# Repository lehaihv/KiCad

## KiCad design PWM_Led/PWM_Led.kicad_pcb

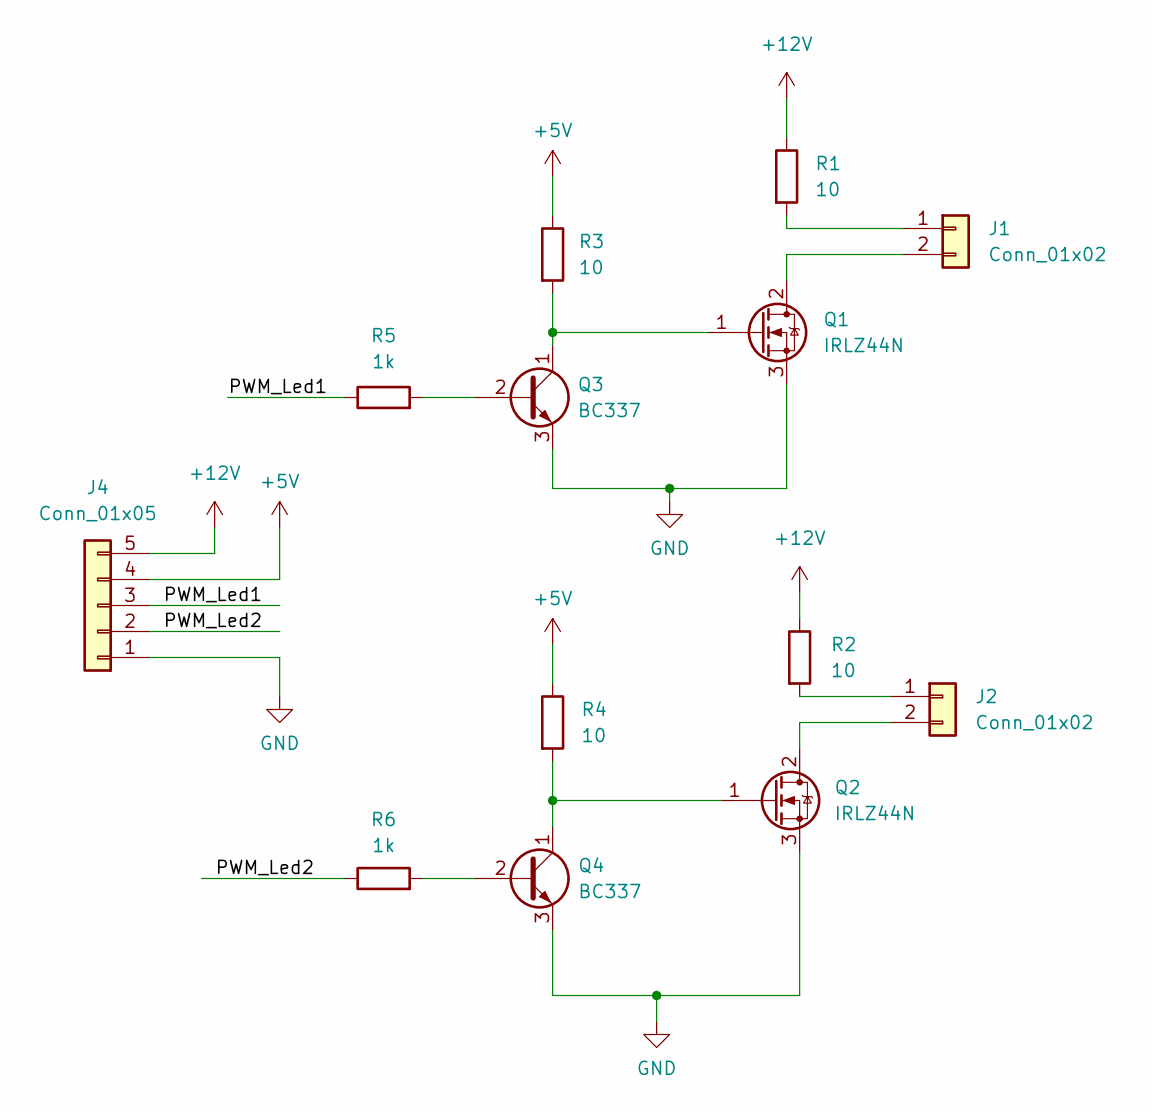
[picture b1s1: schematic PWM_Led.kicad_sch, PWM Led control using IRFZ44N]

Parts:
J1, J2: Conn_01x02
J4: Conn_01x05
Q1, Q2: IRLZ44N; TO-220-3_Vertical
Q3, Q4: BC337; TO-92_Inline
R1, R2, R3, R4: 10
R5, R6: 1k

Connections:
+5V: J4.4, R3.1, R4.1
+12V: J4.5, R1.1, R2.1
/PWM_Led1: J4.3, R5.1
/PWM_Led2: J4.2, R6.1
GND: J4.1, Q1.3 (S), Q2.3 (S), Q3.3 (E), Q4.3 (E)
unnamed: J1.1, R1.2
unnamed: J1.2, Q1.2 (D)
unnamed: J2.1, R2.2
unnamed: J2.2, Q2.2 (D)
unnamed: Q1.1 (G), Q3.1 (C), R3.2
unnamed: Q2.1 (G), Q4.1 (C), R4.2
unnamed: Q3.2 (B), R5.2
unnamed: Q4.2 (B), R6.2

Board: 2 copper layers, 13 parts (0 on the bottom side), 13 nets, no tracks yet.

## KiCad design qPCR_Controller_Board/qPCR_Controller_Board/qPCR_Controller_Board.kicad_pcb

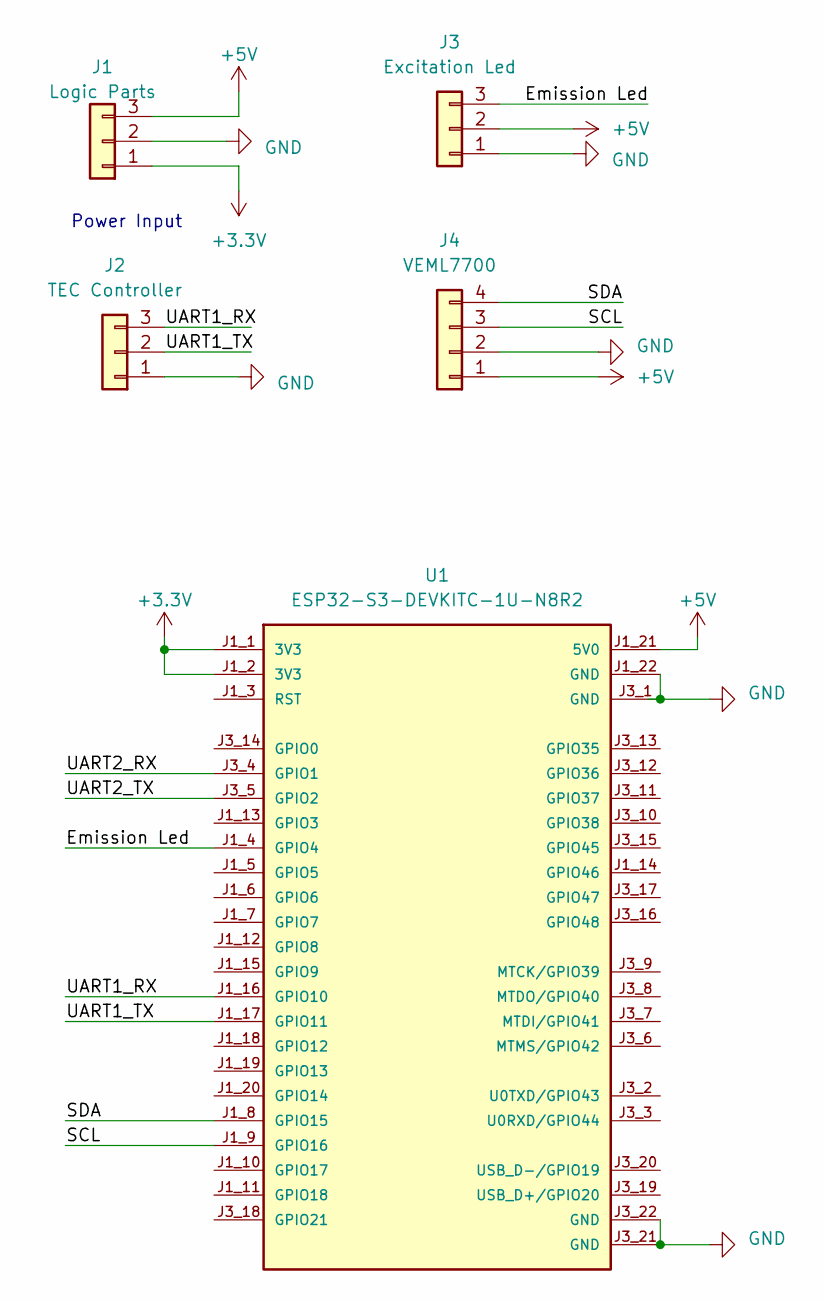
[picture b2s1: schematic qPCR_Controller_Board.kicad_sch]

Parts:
J1: Logic Parts; Molex_KK-254_AE-6410-03A_1x03_P2.54mm_Vertical
J2: TEC Controller; Molex_KK-254_AE-6410-03A_1x03_P2.54mm_Vertical
J3: Excitation Led; Molex_KK-254_AE-6410-03A_1x03_P2.54mm_Vertical
J4: VEML7700; Molex_KK-254_AE-6410-04A_1x04_P2.54mm_Vertical
U1: ESP32-S3-DEVKITC-1U-N8R2; XCVR_ESP32-S3-DEVKITC-1U-N8R2; PARTREV 5.3

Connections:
+3.3V: J1.1, U1.J1_1 (3V3), U1.J1_2 (3V3)
+5V: J1.3, J3.2, J4.1, U1.J1_21 (5V0)
/Emission Led: J3.3, U1.J1_4 (GPIO4)
/SCL: J4.3, U1.J1_9 (GPIO16)
/SDA: J4.4, U1.J1_8 (GPIO15)
/UART1_RX: J2.3, U1.J1_16 (GPIO10)
/UART1_TX: J2.2, U1.J1_17 (GPIO11)
/UART2_RX: U1.J3_4 (GPIO1)
/UART2_TX: U1.J3_5 (GPIO2)
GND: J1.2, J2.1, J3.1, J4.2, U1.J1_22 (GND), U1.J3_1 (GND), U1.J3_21 (GND), U1.J3_22 (GND)

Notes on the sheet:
Power Input

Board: 2 copper layers, 5 parts (0 on the bottom side), 8 nets, no tracks yet.

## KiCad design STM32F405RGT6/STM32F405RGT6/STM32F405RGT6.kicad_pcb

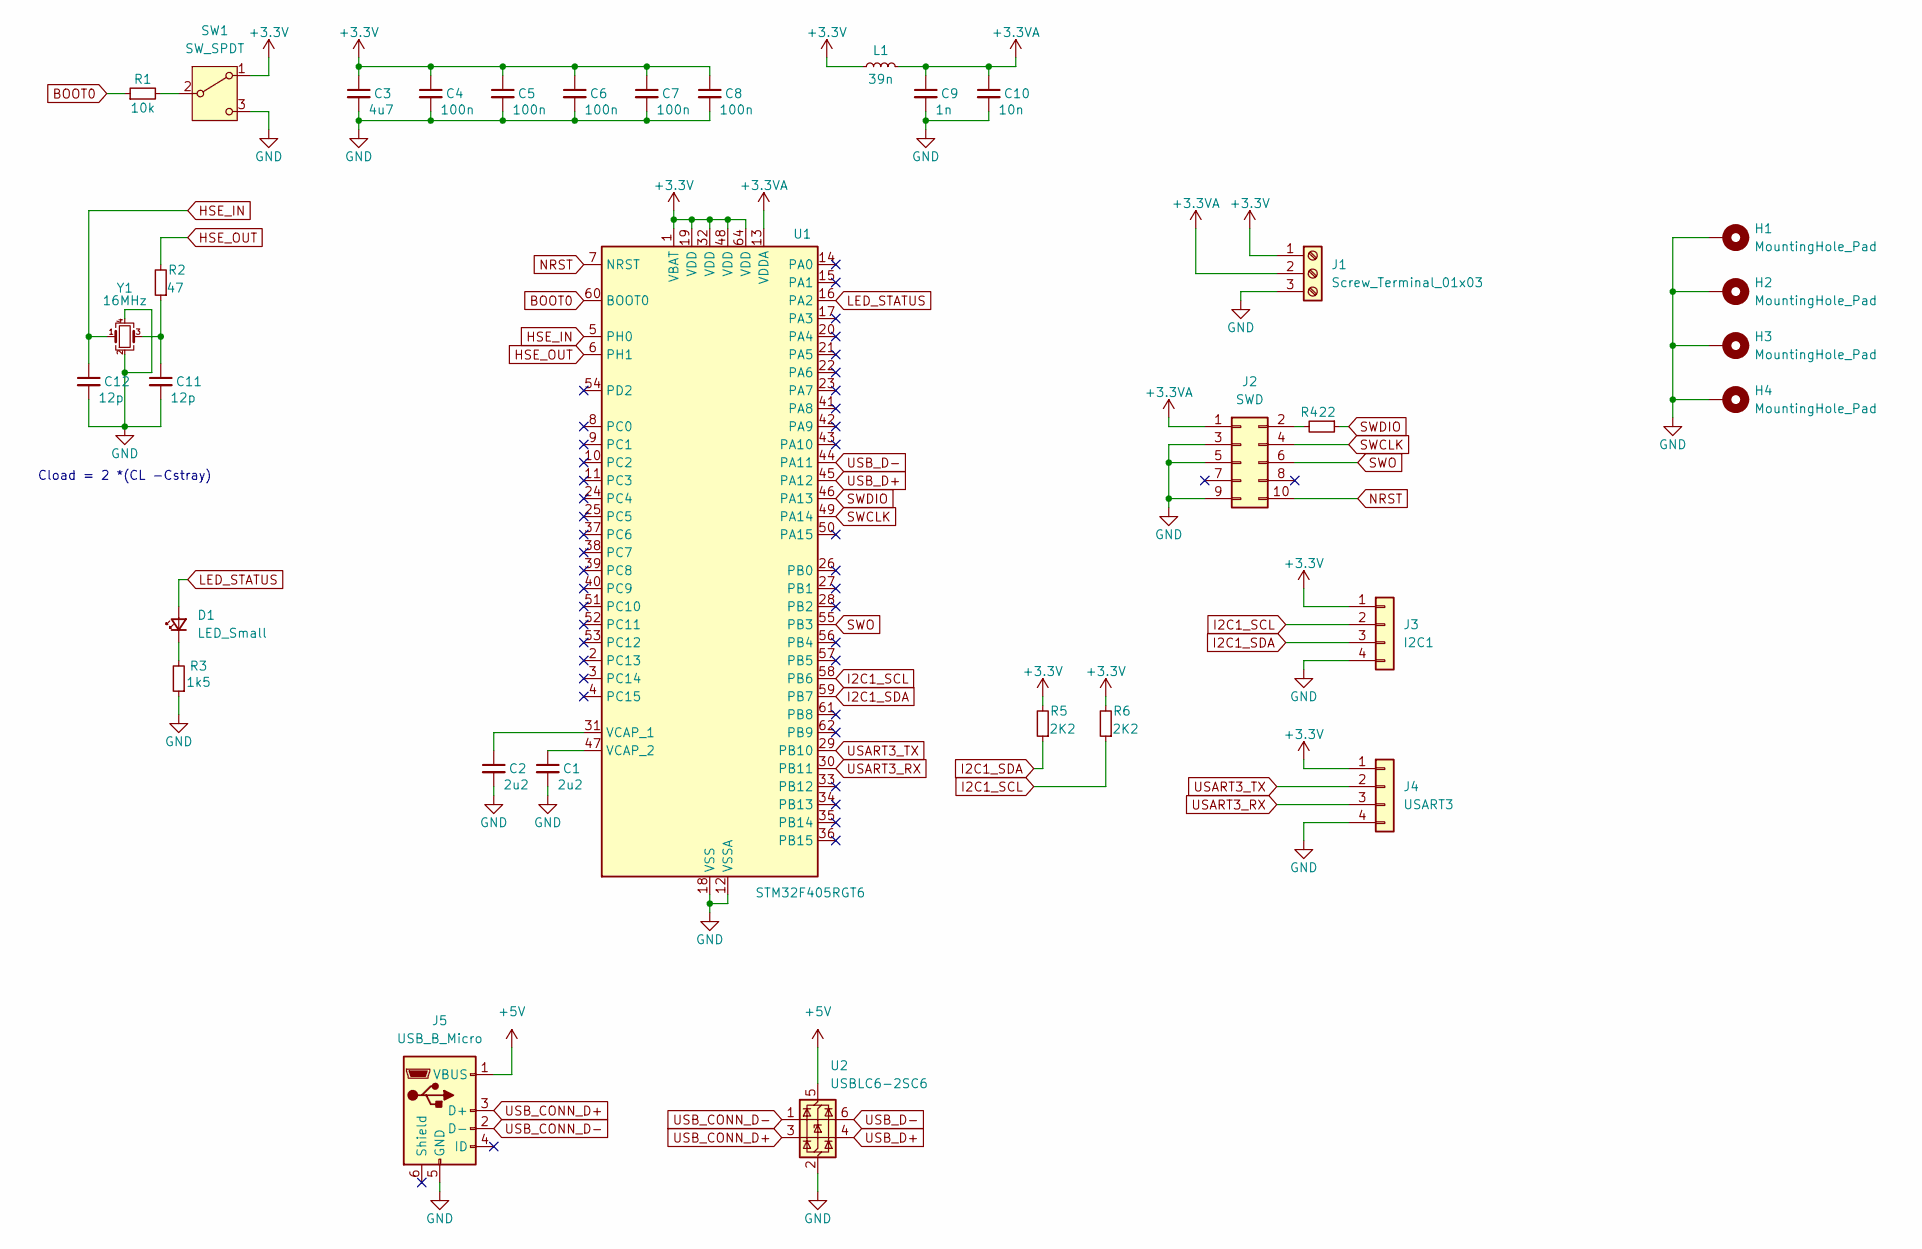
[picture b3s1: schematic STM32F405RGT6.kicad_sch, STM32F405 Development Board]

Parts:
C1, C2: 2u2; C_0603_1608Metric
C3: 4u7; C_0603_1608Metric
C4, C5, C6, C7, C8: 100n; C_0402_1005Metric
C9: 1n; C_0402_1005Metric
C10: 10n; C_0603_1608Metric
C11, C12: 12p; C_0402_1005Metric
D1: LED_Small; LED_0603_1608Metric
H1, H2, H3, H4: MountingHole_Pad; MountingHole_4.3mm_M4_Pad_Via
J1: Screw_Terminal_01x03; TerminalBlock_Phoenix_PT-1,5-3-5.0-H_1x03_P5.00mm_Horizontal
J2: SWD; PinSocket_2x05_P1.27mm_Vertical
J3: I2C1; Molex_PicoBlade_53048-0410_1x04_P1.25mm_Horizontal
J4: USART3; Molex_PicoBlade_53048-0410_1x04_P1.25mm_Horizontal
J5: USB_B_Micro; USB_Micro-B_Amphenol_10118193-0002LF_Horizontal
L1: 39n; L_0402_1005Metric
R1: 10k; R_0603_1608Metric
R2: 47; R_0603_1608Metric
R3: 1k5; R_0603_1608Metric
R4: 22; R_0603_1608Metric
R5, R6: 2K2; R_0603_1608Metric
SW1: SW_SPDT; SW_SPDT_PCM12
U1: STM32F405RGT6; LQFP-64_10x10mm_P0.5mm
U2: USBLC6-2SC6; SOT-23-6
Y1: 16MHz; Crystal_SMD_3225-4Pin_3.2x2.5mm

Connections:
+3.3V: C3.1, C4.1, C5.1, C6.1, C7.1, C8.1, J1.1, J3.1, J4.1, L1.1, R5.2, R6.2, SW1.1 (A), U1.1 (VBAT), U1.19 (VDD), U1.32 (VDD), U1.48 (VDD), U1.64 (VDD)
+3.3VA: C9.1, C10.1, J1.2, J2.1, L1.2, U1.13 (VDDA)
+5V: J5.1 (VBUS), U2.5 (VBUS)
BOOT0: R1.1, U1.60 (BOOT0)
GND: C1.2, C2.2, C3.2, C4.2, C5.2, C6.2, C7.2, C8.2, C9.2, C10.2, C11.2, C12.2, H1.1, H2.1, H3.1, H4.1, J1.3, J2.3, J2.5, J2.9, J3.4, J4.4, J5.5 (GND), R3.1, SW1.3 (C), U1.12 (VSSA), U1.18 (VSS), U1.63 (VSS), U2.2 (GND), Y1.2, Y1.4
HSE_IN: C12.1, U1.5 (PH0), Y1.1
HSE_OUT: R2.2, U1.6 (PH1)
I2C1_SCL: J3.2, R6.1, U1.58 (PB6)
I2C1_SDA: J3.3, R5.1, U1.59 (PB7)
LED_STATUS: D1.2 (A), U1.16 (PA2)
NRST: J2.10, U1.7 (NRST)
unnamed: C11.1, R2.1, Y1.3
unnamed: D1.1 (K), R3.2
unnamed: J2.2, R4.2
unnamed: R1.2, SW1.2 (B)
unnamed: C2.1, U1.31 (VCAP_1)
unnamed: C1.1, U1.47 (VCAP_2)
SWCLK: J2.4, U1.49 (PA14)
SWDIO: R4.1, U1.46 (PA13)
SWO: J2.6, U1.55 (PB3)
USART3_RX: J4.3, U1.30 (PB11)
USART3_TX: J4.2, U1.29 (PB10)
USB_CONN_D+: J5.3 (D+), U2.3 (I/O2)
USB_CONN_D-: J5.2 (D-), U2.1 (I/O1)
USB_D+: U1.45 (PA12), U2.4 (I/O2)
USB_D-: U1.44 (PA11), U2.6 (I/O1)

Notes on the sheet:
Cload = 2 *(CL -Cstray)

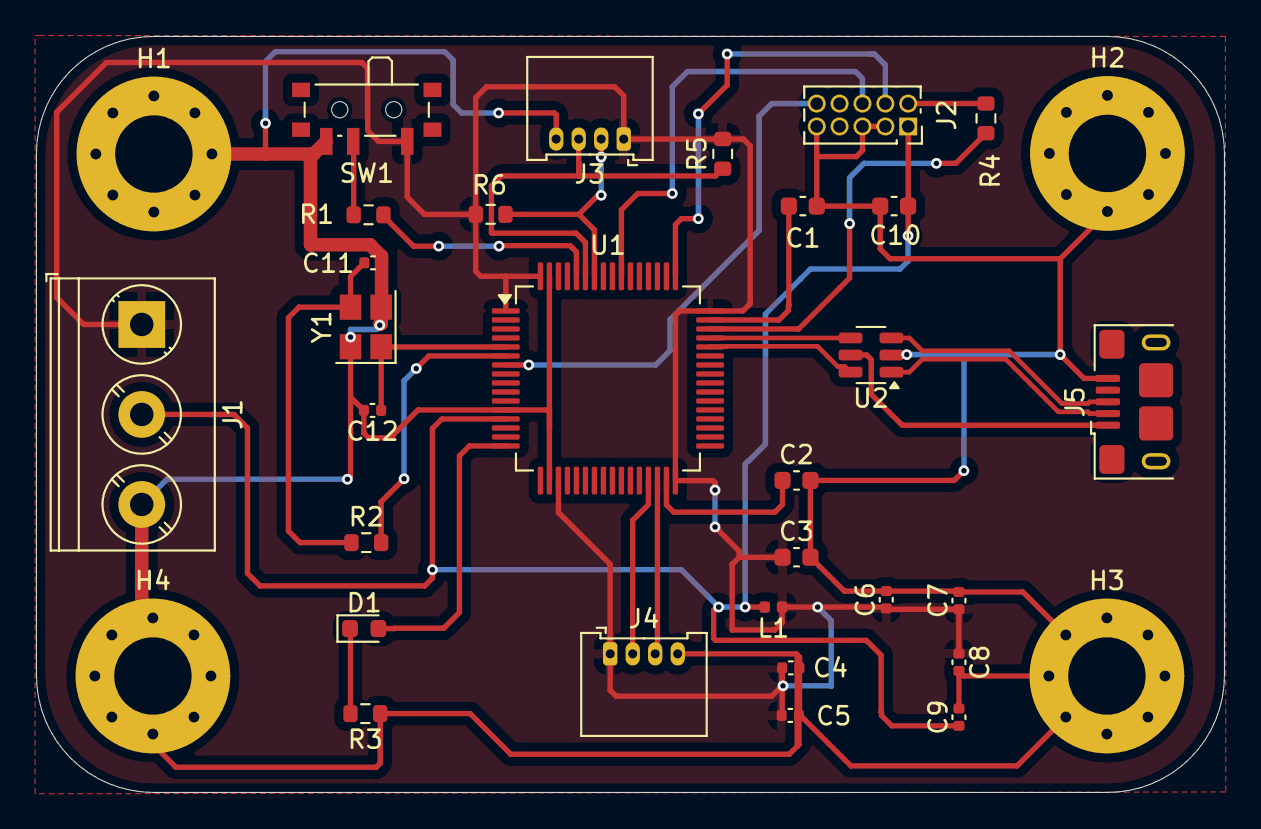
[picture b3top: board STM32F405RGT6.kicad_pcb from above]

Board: 2 copper layers, 66.0 x 42.0 mm, 33 parts (0 on the bottom side), 26 nets.

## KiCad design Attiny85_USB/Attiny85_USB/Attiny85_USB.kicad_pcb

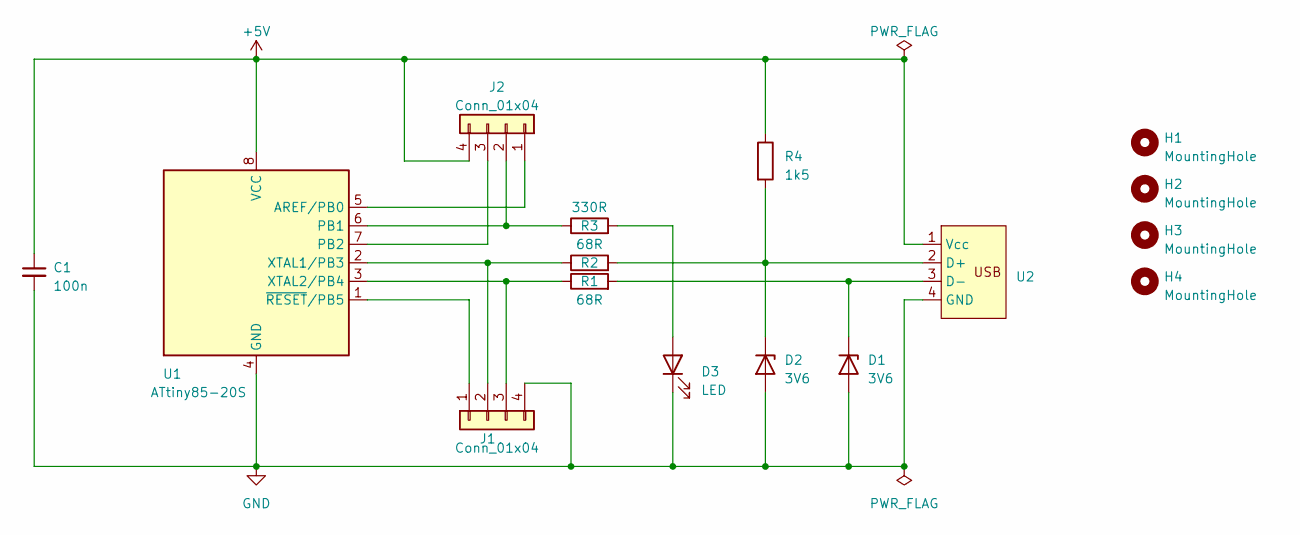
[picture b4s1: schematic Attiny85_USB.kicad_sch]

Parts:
C1: 100n; C_1206_3216Metric_Pad1.33x1.80mm_HandSolder
D1, D2: 3V6; D_SOD-123
D3: LED; LED_1206_3216Metric_Pad1.42x1.75mm_HandSolder
H1, H2, H3, H4: MountingHole; MountingHole_2.2mm_M2
J1, J2: Conn_01x04; PinHeader_1x04_P2.54mm_Vertical
R1, R2: 68R; R_0805_2012Metric_Pad1.20x1.40mm_HandSolder
R3: 330R; R_0805_2012Metric_Pad1.20x1.40mm_HandSolder
R4: 1k5; R_0805_2012Metric_Pad1.20x1.40mm_HandSolder
U1: ATtiny85-20S; SOIC-8W_5.3x5.3mm_P1.27mm
U2: PCB_USB_connector

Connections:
+5V: C1.1, J2.4, R4.1, U1.8 (VCC), U2.1 (Vcc)
GND: C1.2, D1.2 (A), D2.2 (A), D3.1 (K), J1.4, U1.4 (GND), U2.4 (GND)
unnamed: D1.1 (K), R1.2, U2.3 (D-)
unnamed: D2.1 (K), R2.2, R4.2, U2.2 (D+)
unnamed: D3.2 (A), R3.2
unnamed: J1.1, U1.1 (~RESET/PB5)
unnamed: J1.2, R2.1, U1.2 (XTAL1/PB3)
unnamed: J1.3, R1.1, U1.3 (XTAL2/PB4)
unnamed: J2.1, U1.5 (AREF/PB0)
unnamed: J2.2, R3.1, U1.6 (PB1)
unnamed: J2.3, U1.7 (PB2)

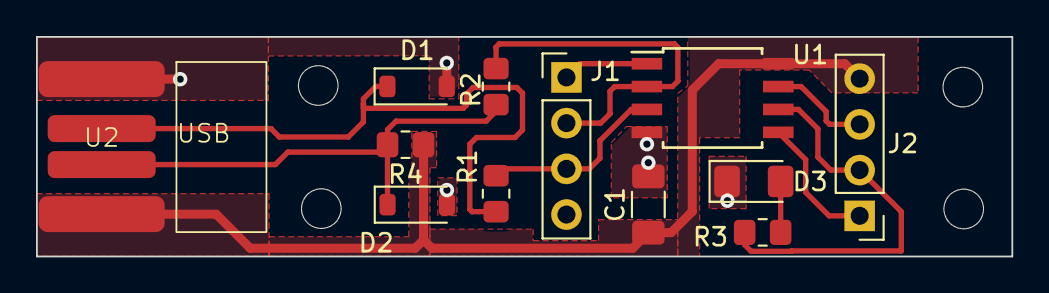
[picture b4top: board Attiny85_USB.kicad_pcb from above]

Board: 2 copper layers, 54.2 x 12.2 mm, 16 parts (0 on the bottom side), 11 nets.

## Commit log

2023-07-22 7740
2023-10-28 Mac 7740
2024-06-18 Dell 7740
2024-08-07 Linux 7740
2024-08-29 Linux 7704
2025-01-23 Mac 5530
